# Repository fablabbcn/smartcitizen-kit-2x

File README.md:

# Smart Citizen Kit 2.X

Welcome to the Smart Citizen Kit main repository. Here you will find the hardware design files and the firmware for the SCK 2.1, SCK 2.2 and SCK 2.3 versions. [Click here for version 2.0](https://github.com/fablabbcn/smartcitizen-kit-20)

## Documentation

* If you want to read more about the Smart Citizen Kit or its sensors please check our [documentation](http://docs.smartcitizen.me/)
* If you just want to **upgrade** your Smart Citizen kit **firmware** please refer to the [Upgrading the Smart Citizen Kit Firmware](https://docs.smartcitizen.me/guides/firmware/upgrading-the-firmware/) guide.
* If you want to change something and build the firmware, use the [Building and flashing the Smart Citizen Kit firmware](https://docs.smartcitizen.me/guides/firmware/edit-the-firmware/) guide.
* The SCK provides a comprehensive command shell over USB to manage all the kits functionalities for advanced users: [Using the Smartcitizen Kit shell](https://docs.smartcitizen.me/guides/getting-started/using-the-shell/) guide.
* A compilation of Smartcitizen hardware work in a single **open publication:** [_Hardware X: Special Issue on Open-Hardware for Environmental Sensing and Instruments_](https://doi.org/10.1016/j.ohx.2019.e00070).
* You can also follow the [forum](https://forum.smartcitizen.me/) for updates and ask questions there for support.

## Development

In this repository you can find:

* The Smart Citizen Kit hardware [design files](./hardware).
* The [bootloader](./bootloader) and [main firmware](./sam) (C++) for the SAMD21 microcontroller.
* The [main firmware](./esp) for the ESP8266 microcontroller.
* A [mobile web UI](./mock-api) for setting up the kit.

## Related Smart Citizen repositories

* Platform Core API [github.com/fablabbcn/smartcitizen-api](https://github.com/fablabbcn/smartcitizen-api)
* Platform Web [github.com/fablabbcn/smartcitizen-web](https://github.com/fablabbcn/smartcitizen-web)
* Platform Onboarding [github.com/fablabbcn/smartcitizen-onboarding-app](https://github.com/fablabbcn/smartcitizen-onboarding-app)
* Kit Enclosures [github.com/fablabbcn/smartcitizen-enclosures](https://github.com/fablabbcn/smartcitizen-enclosures)
* Useful software resources for communities [github.com/fablabbcn/smartcitizen-toolkit](https://github.com/fablabbcn/smartcitizen-toolkit)
* Advanced data analysis tools [github.com/fablabbcn/smartcitizen-data](https://github.com/fablabbcn/smartcitizen-data)
* Python API connector [github.com/fablabbcn/smartcitizen-connector](https://github.com/fablabbcn/smartcitizen-connector)
* Analog Sensor Board [github.com/fablabbcn/smartcitizen-analog-sensor-board](https://github.com/fablabbcn/smartcitizen-analog-sensor-board)
* PM Board [github.com/fablabbcn/smartcitizen-kit-pm-board](https://github.com/fablabbcn/smartcitizen-kit-pm-board)

## License

All the software unless stated is released under [GNU GPL v3.0](https://github.com/fablabbcn/smartcitizen-kit-20/blob/master/LICENSE) and the hardware design files under [CERN OHL v1.2](https://github.com/fablabbcn/smartcitizen-kit-20/blob/master/hardware/LICENSE)

## Funding

This work has received funding from the European Union's Horizon 2020 research and innovation program under the grant agreement [No. 689954](https://cordis.europa.eu/project/rcn/202639_en.html)

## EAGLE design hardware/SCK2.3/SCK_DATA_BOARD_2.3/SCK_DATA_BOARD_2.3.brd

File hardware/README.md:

Smart Citizen Kit 2.X Hardware
==============================

This folder contains the Eagle design files for the Smart Citizen Kit 2.X, as well as the silkscreen and manufacturing files:

## SCK 2.1 (discontinued for sensor availability)

- Production files:
    + [SCK 2.1 Data Board production files](SCK2.1/SCK_DATA_BOARD_2.1/SCK_DATA_BOARD_2.1_PRODUCTION.zip)
    + [SCK 2.1 Urban Board production files](SCK2.1/SCK_URBAN_BOARD_2.1/SCK_URBAN_BOARD_2.1_PRODUCTION.zip)
- Design files:
    + [SCK 2.1 Data Board design files](SCK2.1/SCK_DATA_BOARD_2.1)
    + [SCK 2.1 Urban Board design files](SCK2.1/SCK_URBAN_BOARD_2.1)
- [Silkscreen](SCK2.1/SCK_2.1_SILKSCREEN.pdf)
- [Test plan](SCK2.1/test/SCK_2.1_TESTPLAN.pdf), also [at the docs](https://docs.smartcitizen.me/assets/notes/SCK_2.1_TESTPLAN.pdf)
- [Bootloader](SCK2.1/bootloader)

## SCK 2.2 (only for some projects)

- Production files:
    + [SCK 2.2 Data Board production files](SCK2.2/SCK_DATA_BOARD_2.2/SCK_DATA_BOARD_2.2_PRODUCTION.zip)
    + [SCK 2.2 Urban Board production files](SCK2.2/SCK_URBAN_BOARD_2.2/SCK_URBAN_BOARD_2.2_PRODUCTION.zip)
- Design files:
    + [SCK 2.2 Data Board design files](SCK2.2/SCK_DATA_BOARD_2.2)
    + [SCK 2.2 Urban Board design files](SCK2.2/SCK_URBAN_BOARD_2.2)
- [Silkscreen](SCK2.2/SCK2.2_SILKSCREEN.pdf)
- [Test plan](SCK2.2/test/SCK2.2_TESTPLAN.pdf)
- [Bootloader](SCK2.2/bootloader)

## SCK 2.3 (current)

- Production files:
    + [SCK 2.3 Data Board production files](SCK2.3/SCK_DATA_BOARD_2.3/SCK_DATA_BOARD_2.3_PRODUCTION.zip)
    + [SCK 2.3 Urban Board production files](SCK2.3/SCK_URBAN_BOARD_2.3/SCK_URBAN_BOARD_2.3_PRODUCTION.zip)
- Design files:
    + [SCK 2.3 Data Board design files](SCK2.3/SCK_DATA_BOARD_2.3)
    + [SCK 2.3 Urban Board design files](SCK2.3/SCK_URBAN_BOARD_2.3)
- [Test plan](SCK2.3/test/SCK2.3_TESTPLAN.pdf)
- [Bootloader](SCK2.3/bootloader)

Note: for Data Board schematics, see [SCK_DATA_2.1 folder](SCK2.1/SCK_DATA_BOARD_2.1)

## License

All the software is released under [GNU GPL v3.0](../LICENSE) and the hardware design files under [CERN OHL v1.2](LICENSE)

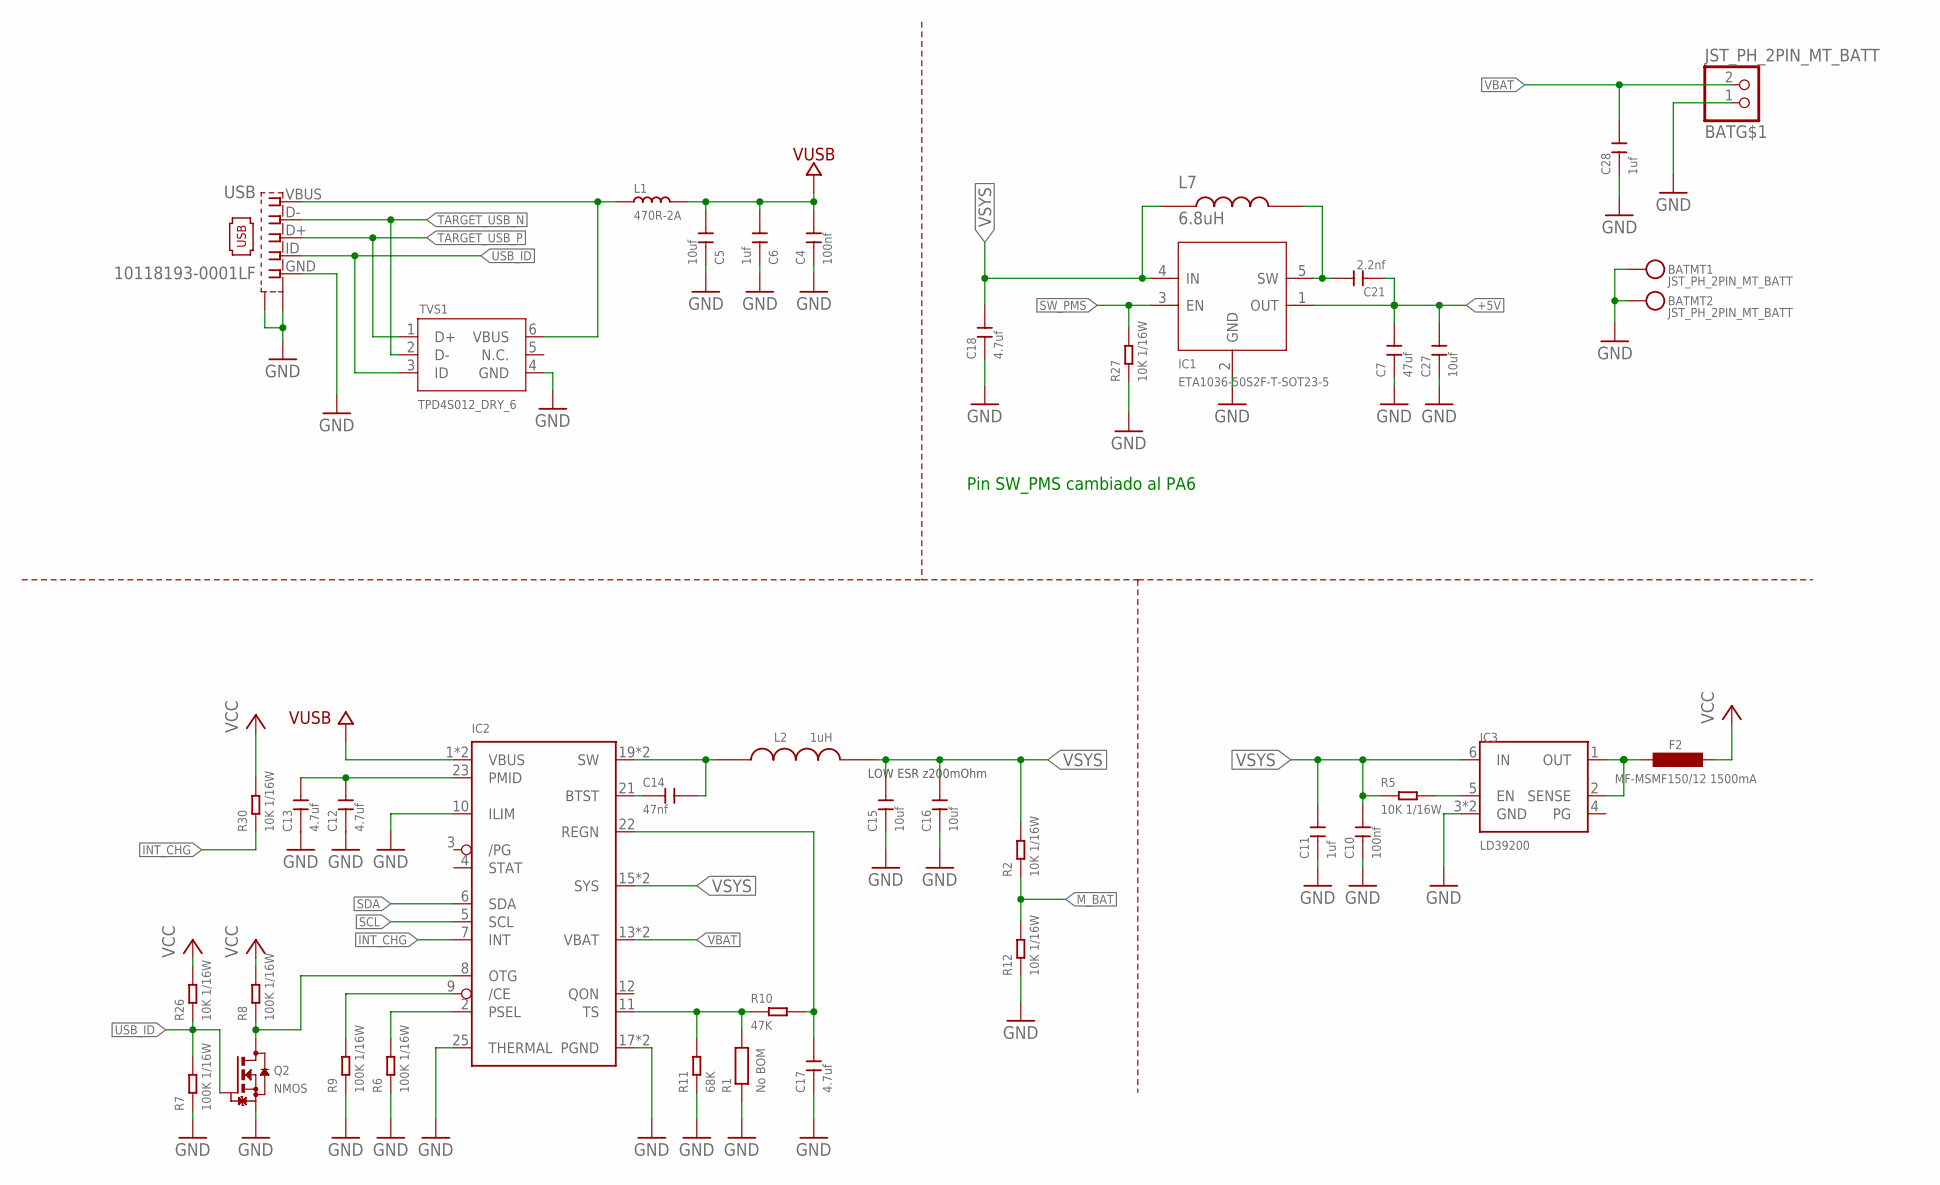
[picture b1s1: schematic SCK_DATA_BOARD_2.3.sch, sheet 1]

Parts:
BAT: JST_PH_2PIN_MT_BATT; JSTPH2_BATT
C4, C10: 100nf; C0402
C5: 10uf; C1206
C6, C11, C28: 1uf; C0805
C7: 47uf; C0805
C12, C13, C17, C18: 4.7uf; C0603
C14: 47nf; C0402
C15, C16, C27: 10uf; C0603
C21: 2.2nf; C0402
F2: MF-MSMF150/12 1500mA; L1812
IC1: ETA1036-50S2F-T-SOT23-5; SOT-23-5
IC2: BQ24259_VQFN(24); 24-PIN_VQFN_THPAD
IC3: LD39200; DFN6_3X3MM
L1: 470R-2A; L0805
L2: 1uH; HANGAR_C1210
L7: 6.8uH; IND_BOURNS_SRN3015TA_3X3_SMD
Q2: NMOS; NMOS_UMT3
R1: No BOM; HANGAR_R0402
R2, R5, R12, R26, R27, R30: 10K 1/16W; R0402
R6, R7, R8, R9: 100K 1/16W; R0402
R10: 47K; R0402
R11: 68K; R0402
TVS1: TPD4S012_DRY_6; DRY6
USB: 10118193-0001LF; CON2_USB_MICRO_B_AT

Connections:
+5V: C7.2, C21.1, C27.2, IC1.1 (OUT); also elsewhere on the board
BTST: C14.1, IC2.21 (BTST)
GND: BAT.1, BAT.NC1, BAT.NC2, C4.1, C5.1, C6.1, C7.1, C10.1, C11.1, C12.1, C13.1, C15.1, C16.1, C17.1, C18.1, C27.1, C28.1, IC1.2 (GND), IC2.10 (ILIM), IC2.17 (PGND), IC2.18 (PGND), IC2.25 (THERMAL), IC3.3 (GND), IC3.7 (GND), Q2.1 (S), R1.1, R6.1, R7.1, R9.1, R11.1, R12.1, R27.1, TVS1.4 (GND), USB.GND (5), USB.P$1 (S1), USB.P$2 (S1), USB.P$3 (S1), USB.P$4 (S1), USB.P$5 (S1), USB.P$6 (S1), USB.P$7 (S1), USB.P$8 (S1), USB.S1 (S2), USB.S2, USB.S3 (S2), USB.S4 (S2), USB.S5 (S2), USB.S6 (S2); also elsewhere on the board
INT_CHG: IC2.7 (INT), R30.1; also elsewhere on the board
M_BAT: R2.1, R12.2; also elsewhere on the board
unnamed: IC3.5 (EN), R5.2
unnamed: L1.1, TVS1.6 (VBUS), USB.VBUS (1)
unnamed: C21.2, IC1.5 (SW), L7.P$2
unnamed: C17.2, IC2.22 (REGN), R10.2
unnamed: C12.2, C13.2, IC2.23 (PMID)
unnamed: IC2.11 (TS), R1.2, R10.1, R11.2
unnamed: IC2.9 (/CE), R9.2
OTG: IC2.8 (OTG), Q2.3 (D), R8.1
PSEL: IC2.2 (PSEL), R6.2
SCL: IC2.5 (SCL); also elsewhere on the board
SDA: IC2.6 (SDA); also elsewhere on the board
SW: C14.2, IC2.19 (SW), IC2.20 (SW), L2.1
SW_PMS: IC1.3 (EN), R27.2; also elsewhere on the board
TARGET_USB_N: TVS1.2 (D-), USB.D- (2); also elsewhere on the board
TARGET_USB_P: TVS1.1 (D+), USB.D+ (3); also elsewhere on the board
USB_ID: Q2.2 (G), R7.2, R26.1, TVS1.3 (ID), USB.ID (4)
VBAT: BAT.2, C28.2, IC2.13 (VBAT), IC2.14 (VBAT)
VCC: F2.1, R8.2, R26.2, R30.2; also elsewhere on the board
VCC_SOURCE: F2.2, IC3.1 (OUT), IC3.2 (SENSE)
VSYS: C10.2, C11.2, C15.2, C16.2, C18.2, IC1.4 (IN), IC2.15 (SYS), IC2.16 (SYS), IC3.6 (IN), L2.2, L7.P$1, R2.2, R5.1
VUSB: C4.2, C5.2, C6.2, IC2.1 (VBUS), IC2.24 (VBUS), L1.2

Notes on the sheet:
LOW ESR z200mOhm
Pin SW_PMS cambiado al PA6

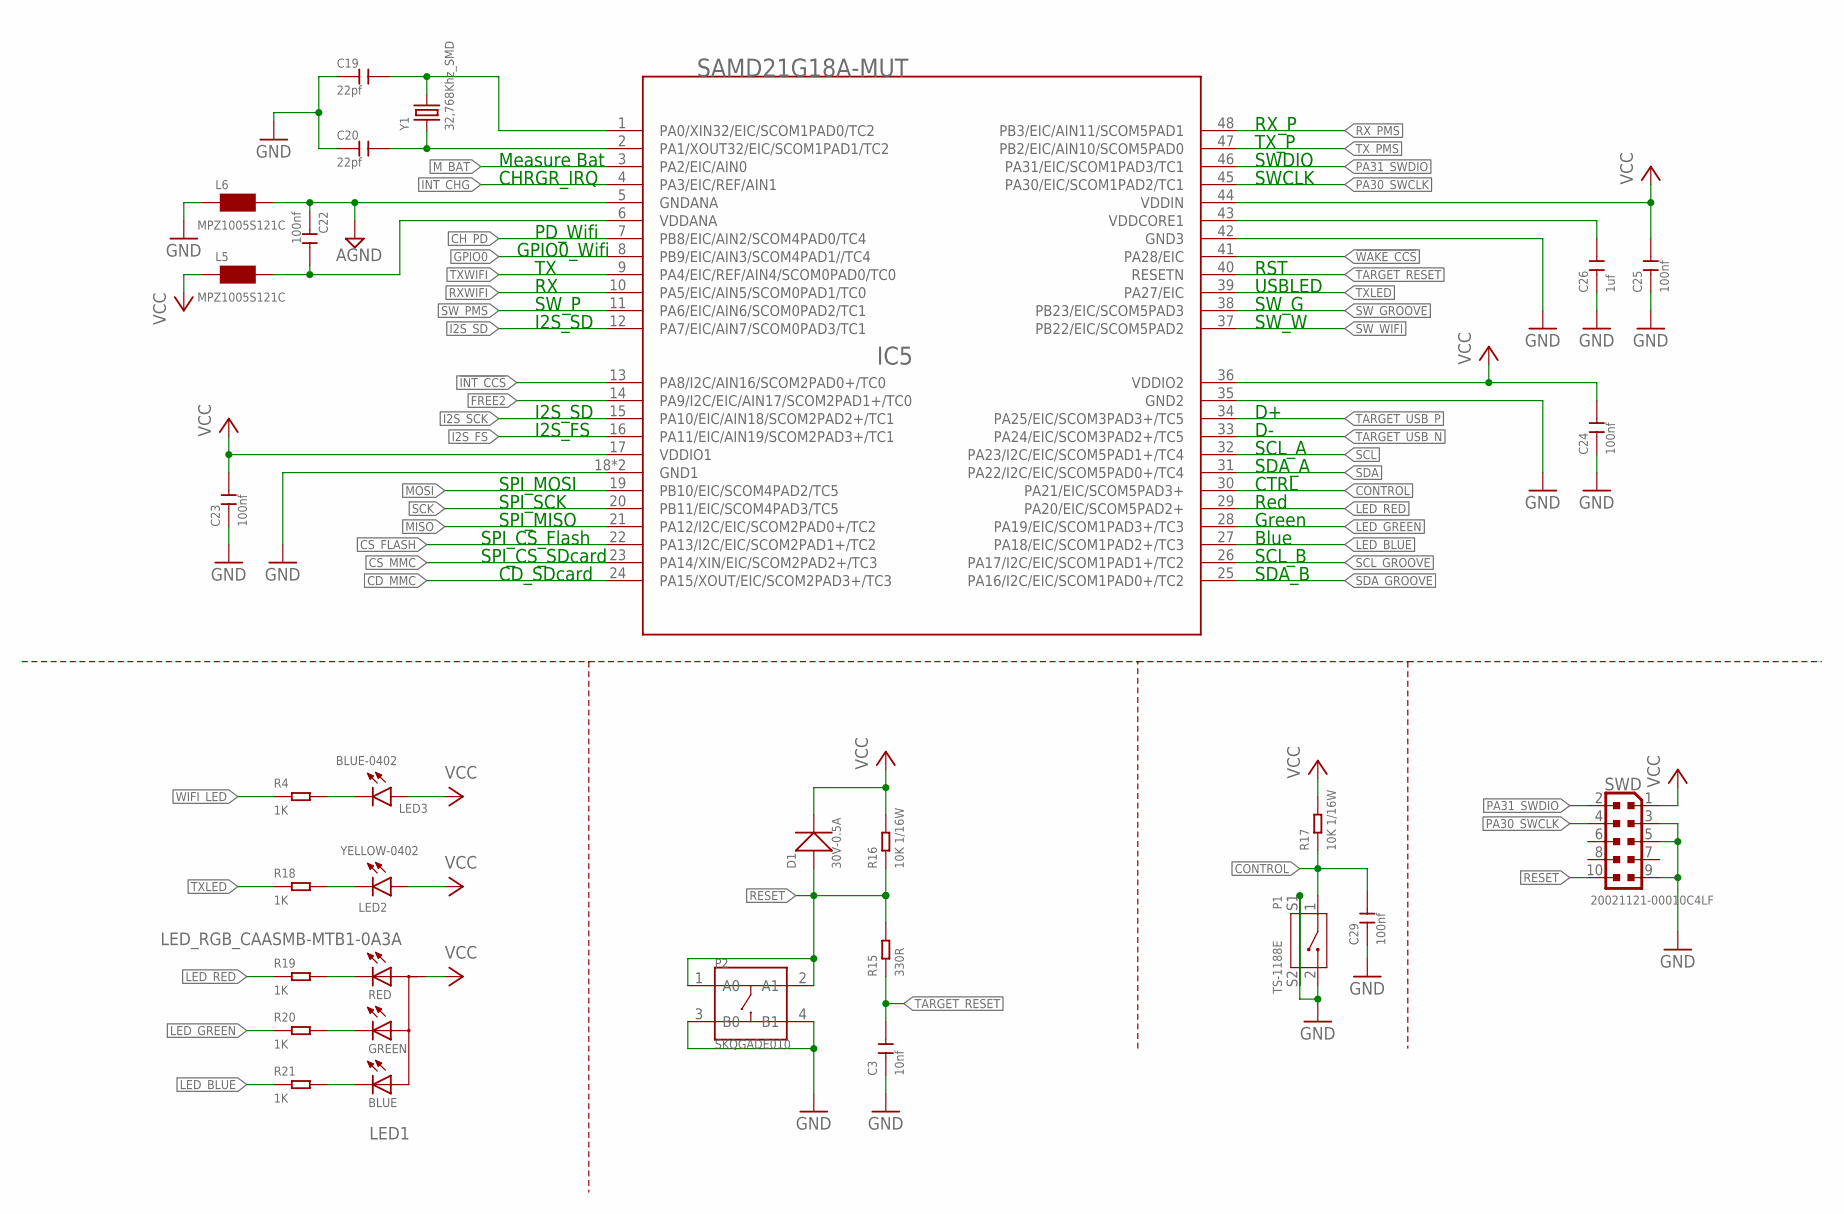
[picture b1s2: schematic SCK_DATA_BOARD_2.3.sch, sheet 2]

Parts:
C3: 10nf; C0402
C19, C20: 22pf; C0402
C22, C23, C24, C25, C29: 100nf; C0402
C26: 1uf; C0805
D1: 30V-0.5A; SOD-323
IC5: SAMD21G18A-MUT; QFN48-7X7
L5, L6: MPZ1005S121C; 0402
LED1: LED_RGB_CAASMB-MTB1-0A3A; HANGAR_P-LCC-4
LED2: YELLOW-0402; CHIPLED_0402_YELLOW
LED3: BLUE-0402; CHIPLED_0402_BLUE
P1: TS-1188E; SW4-SMD-7.0X3.5X3.5MM-90D
P2: SKQGADE010; SW4-SMD-5.2X5.2X1.5MM
R4, R18, R19, R20, R21: 1K; R0402
R15: 330R; R0402
R16, R17: 10K 1/16W; R0402
SWD: 20021121-00010C4LF; 2X05_SMD_1.27MM
Y1: 32,768Khz_SMD; CRISTALLI_RESONATOR_EPSON_FC_145

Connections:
!INT_CCS: IC5.13 (PA8/I2C/AIN16/SCOM2PAD0+/TC0); also elsewhere on the board
!WAKE_CCS: IC5.41 (PA28/EIC); also elsewhere on the board
AGND: C22.1, IC5.5 (GNDANA), L6.2
AVCC: C22.2, IC5.6 (VDDANA), L5.2
CD_MMC: IC5.24 (PA15/XOUT/EIC/SCOM2PAD3+/TC3); also elsewhere on the board
CH_PD: IC5.7 (PB8/EIC/AIN2/SCOM4PAD0/TC4); also elsewhere on the board
CONTROL: C29.2, IC5.30 (PA21/EIC/SCOM5PAD3+), P1.1, R17.1
CS_FLASH: IC5.22 (PA13/I2C/EIC/SCOM2PAD1+/TC2); also elsewhere on the board
CS_MMC: IC5.23 (PA14/XIN/EIC/SCOM2PAD2+/TC3); also elsewhere on the board
FREE2: IC5.14 (PA9/I2C/EIC/AIN17/SCOM2PAD1+/TC0); also elsewhere on the board
GND: C3.1, C19.1, C20.1, C23.1, C24.1, C25.1, C26.1, C29.1, IC5.18 (GND1), IC5.35 (GND2), IC5.42 (GND3), IC5.TP (GND1), L6.1, P1.2, P1.S1, P1.S2, P2.3 (B0), P2.4 (B1), SWD.3, SWD.5, SWD.9; also elsewhere on the board
GPIO0: IC5.8 (PB9/EIC/AIN3/SCOM4PAD1//TC4); also elsewhere on the board
I2S_FS: IC5.16 (PA11/EIC/AIN19/SCOM2PAD3+/TC1); also elsewhere on the board
I2S_SCK: IC5.15 (PA10/EIC/AIN18/SCOM2PAD2+/TC1); also elsewhere on the board
I2S_SD: IC5.12 (PA7/EIC/AIN7/SCOM0PAD3/TC1); also elsewhere on the board
INT_CHG: IC5.4 (PA3/EIC/REF/AIN1); also elsewhere on the board
LED_BLUE: IC5.27 (PA18/EIC/SCOM1PAD2+/TC3), R21.1
LED_GREEN: IC5.28 (PA19/EIC/SCOM1PAD3+/TC3), R20.1
LED_RED: IC5.29 (PA20/EIC/SCOM5PAD2+), R19.1
MISO: IC5.21 (PA12/I2C/EIC/SCOM2PAD0+/TC2); also elsewhere on the board
MOSI: IC5.19 (PB10/EIC/SCOM4PAD2/TC5); also elsewhere on the board
M_BAT: IC5.3 (PA2/EIC/AIN0); also elsewhere on the board
unnamed: LED2.K (C), R18.2
unnamed: LED1.2 (GREEN), R20.2
unnamed: LED3.K (C), R4.2
unnamed: LED1.1 (RED), R19.2
unnamed: LED1.3 (BLUE), R21.2
PA00_XIN32: C19.2, IC5.1 (PA0/XIN32/EIC/SCOM1PAD0/TC2), Y1.P$2 (2)
PA01_XOUT32: C20.2, IC5.2 (PA1/XOUT32/EIC/SCOM1PAD1/TC2), Y1.P$1 (1)
PA30_SWCLK: IC5.45 (PA30/EIC/SCOM1PAD2/TC1), SWD.4
PA31_SWDIO: IC5.46 (PA31/EIC/SCOM1PAD3/TC1), SWD.2
RESET: D1.+, P2.1 (A0), P2.2 (A1), R15.2, R16.1, SWD.10; also elsewhere on the board
RXWIFI: IC5.10 (PA5/EIC/AIN5/SCOM0PAD1/TC0); also elsewhere on the board
RX_PMS: IC5.48 (PB3/EIC/AIN11/SCOM5PAD1); also elsewhere on the board
SCK: IC5.20 (PB11/EIC/SCOM4PAD3/TC5); also elsewhere on the board
SCL: IC5.32 (PA23/I2C/EIC/SCOM5PAD1+/TC4); also elsewhere on the board
SCL_GROOVE: IC5.26 (PA17/I2C/EIC/SCOM1PAD1+/TC2); also elsewhere on the board
SDA: IC5.31 (PA22/I2C/EIC/SCOM5PAD0+/TC4); also elsewhere on the board
SDA_GROOVE: IC5.25 (PA16/I2C/EIC/SCOM1PAD0+/TC2); also elsewhere on the board
SW_GROOVE: IC5.38 (PB23/EIC/SCOM5PAD3); also elsewhere on the board
SW_PMS: IC5.11 (PA6/EIC/AIN6/SCOM0PAD2/TC1); also elsewhere on the board
SW_WIFI: IC5.37 (PB22/EIC/SCOM5PAD2); also elsewhere on the board
TARGET_RESET: C3.2, IC5.40 (RESETN), R15.1
TARGET_USB_N: IC5.33 (PA24/EIC/SCOM3PAD2+/TC5); also elsewhere on the board
TARGET_USB_P: IC5.34 (PA25/EIC/SCOM3PAD3+/TC5); also elsewhere on the board
TXLED: IC5.39 (PA27/EIC), R18.1
TXWIFI: IC5.9 (PA4/EIC/REF/AIN4/SCOM0PAD0/TC0); also elsewhere on the board
TX_PMS: IC5.47 (PB2/EIC/AIN10/SCOM5PAD0); also elsewhere on the board
VCC: C23.2, C24.2, C25.2, D1.-, IC5.17 (VDDIO1), IC5.36 (VDDIO2), IC5.44 (VDDIN), L5.1, LED1.4 (A), LED2.A, LED3.A, R16.2, R17.2, SWD.1; also elsewhere on the board
VDDCORE: C26.2, IC5.43 (VDDCORE1)
WIFI_LED: R4.1; also elsewhere on the board

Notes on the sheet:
Blue
Green
SCL_B
SDA_B
Red
CTRL
SW_G
SW_W
SDA_A
SCL_A
USBLED
RST
SWDIO
SWCLK
PD_Wifi
GPIO0_Wifi
I2S_SD
Measure Bat
CHRGR_IRQ
I2S_FS
SPI_MOSI
SPI_SCK
SPI_MISO
SPI_CS_Flash
SPI_CS_SDcard
CD_SDcard
SW_P
RX_P
TX_P

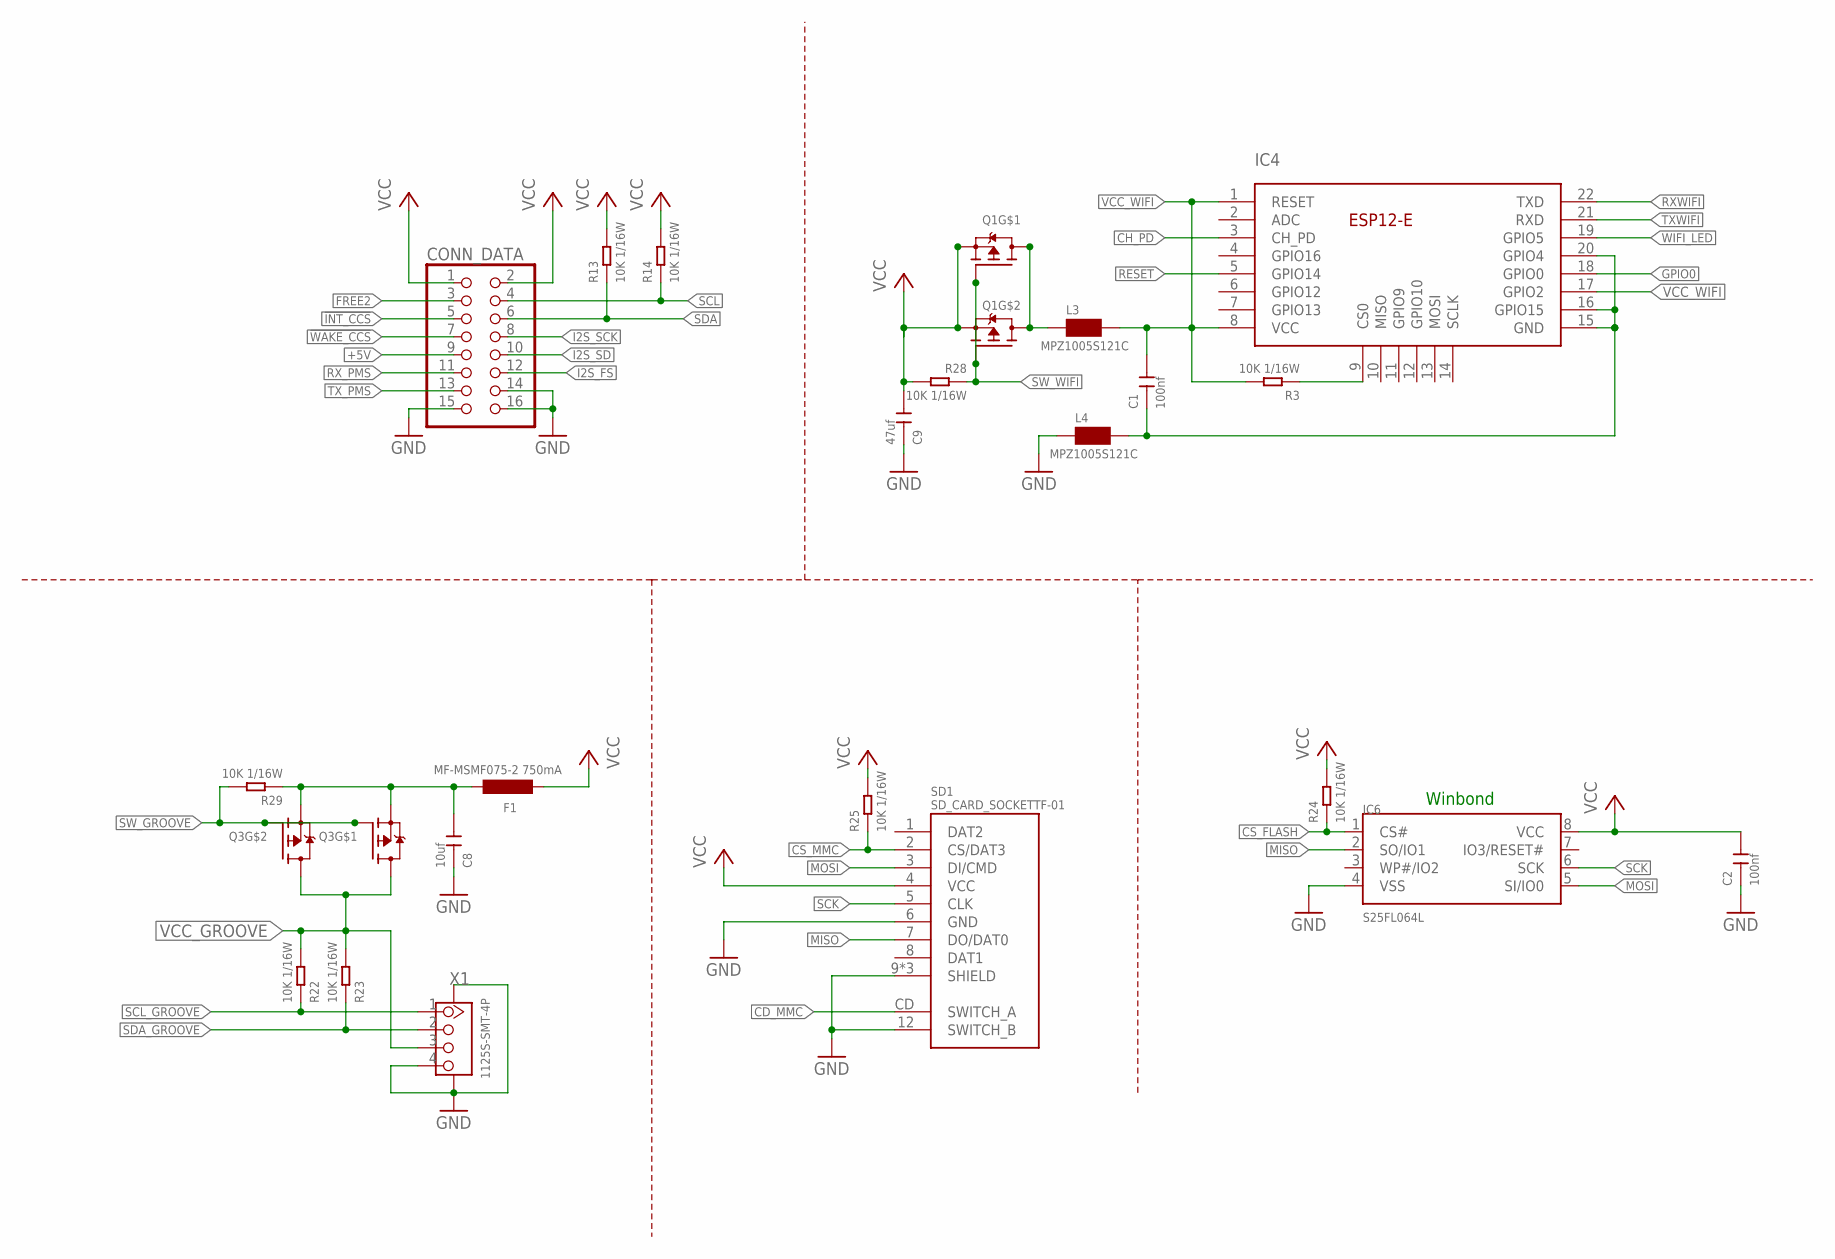
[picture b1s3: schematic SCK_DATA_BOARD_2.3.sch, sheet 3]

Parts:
C1, C2: 100nf; C0402
C8: 10uf; C1206
C9: 47uf; C1210
CONN_DATA: PINHD_2X8FEM_SMD; PINHD_2X8_SMD_FEMALE_UNHOLED
F1: MF-MSMF075-2 750mA; L1812
IC4: HANGAR_ESP-12-E; HANGAR_ESP12-E
IC6: S25FL064L; SOIC_8-208MILS
L3, L4: MPZ1005S121C; 0402
Q1: PMOS; POWERPAK-SC70-6L; MPN SIA923AEDJ-T1-GE3
Q3: PMOS; POWERPAK-SC70-6L
R3, R13, R14, R22, R23, R24, R25, R28, R29: 10K 1/16W; R0402
SD1: SD_CARD_SOCKETTF-01; TF-01; MPN 320090008
X1: 1125S-SMT-4P; CONNECTOR-NEW_HW4-SMD-2.0; MPN 320110030

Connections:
!INT_CCS: CONN_DATA.5; also elsewhere on the board
!WAKE_CCS: CONN_DATA.7; also elsewhere on the board
+5V: CONN_DATA.9; also elsewhere on the board
CD_MMC: SD1.CD (SWITCH_A); also elsewhere on the board
CH_PD: IC4.3 (CH_PD); also elsewhere on the board
CS_FLASH: IC6.1 (CS#), R24.1; also elsewhere on the board
CS_MMC: R25.1, SD1.2 (CS/DAT3); also elsewhere on the board
FREE2: CONN_DATA.3; also elsewhere on the board
GND: C2.1, C8.1, C9.1, CONN_DATA.14, CONN_DATA.15, CONN_DATA.16, IC6.4 (VSS), L4.2, SD1.6 (GND), SD1.9 (SHIELD), SD1.10 (SHIELD), SD1.11 (SHIELD), SD1.12 (SWITCH_B), X1.4, X1.SS1, X1.SS2; also elsewhere on the board
GND_WIFI: C1.1, IC4.15 (GND), IC4.16 (GPIO15), IC4.20 (GPIO4), L4.1
GPIO0: IC4.18 (GPIO0); also elsewhere on the board
I2S_FS: CONN_DATA.12; also elsewhere on the board
I2S_SCK: CONN_DATA.8; also elsewhere on the board
I2S_SD: CONN_DATA.10; also elsewhere on the board
MISO: IC6.2 (SO/IO1), SD1.7 (DO/DAT0); also elsewhere on the board
MOSI: IC6.5 (SI/IO0), SD1.3 (DI/CMD); also elsewhere on the board
unnamed: L3.2, Q1.3 (D), Q1.6 (D), Q1.TP1 (D), Q1.TP2 (D)
unnamed: IC4.9 (CS0), R3.1
RESET: IC4.5 (GPIO14); also elsewhere on the board
RXWIFI: IC4.22 (TXD); also elsewhere on the board
RX_PMS: CONN_DATA.11; also elsewhere on the board
SCK: IC6.6 (SCK), SD1.5 (CLK); also elsewhere on the board
SCL: CONN_DATA.4, R14.1; also elsewhere on the board
SCL_GROOVE: R22.1, X1.1; also elsewhere on the board
SDA: CONN_DATA.6, R13.1; also elsewhere on the board
SDA_GROOVE: R23.1, X1.2; also elsewhere on the board
SW_GROOVE: Q3.2 (G), Q3.5 (G), R29.2; also elsewhere on the board
SW_WIFI: Q1.2 (G), Q1.5 (G), R28.1; also elsewhere on the board
TXWIFI: IC4.21 (RXD); also elsewhere on the board
TX_PMS: CONN_DATA.13; also elsewhere on the board
VCC: C2.2, C9.2, CONN_DATA.1, CONN_DATA.2, F1.2, IC6.8 (VCC), Q1.1 (S), Q1.4 (S), R13.2, R14.2, R24.2, R25.2, R28.2, SD1.4 (VCC); also elsewhere on the board
VCC_GROOVE: Q3.3 (D), Q3.6 (D), Q3.TP1 (D), Q3.TP2 (D), R22.2, R23.2, X1.3
VCC_GROOVE_0: C8.2, F1.1, Q3.1 (S), Q3.4 (S), R29.1
VCC_WIFI: C1.2, IC4.1 (RESET), IC4.8 (VCC), IC4.17 (GPIO2), L3.1, R3.2
WIFI_LED: IC4.19 (GPIO5); also elsewhere on the board

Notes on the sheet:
Winbond

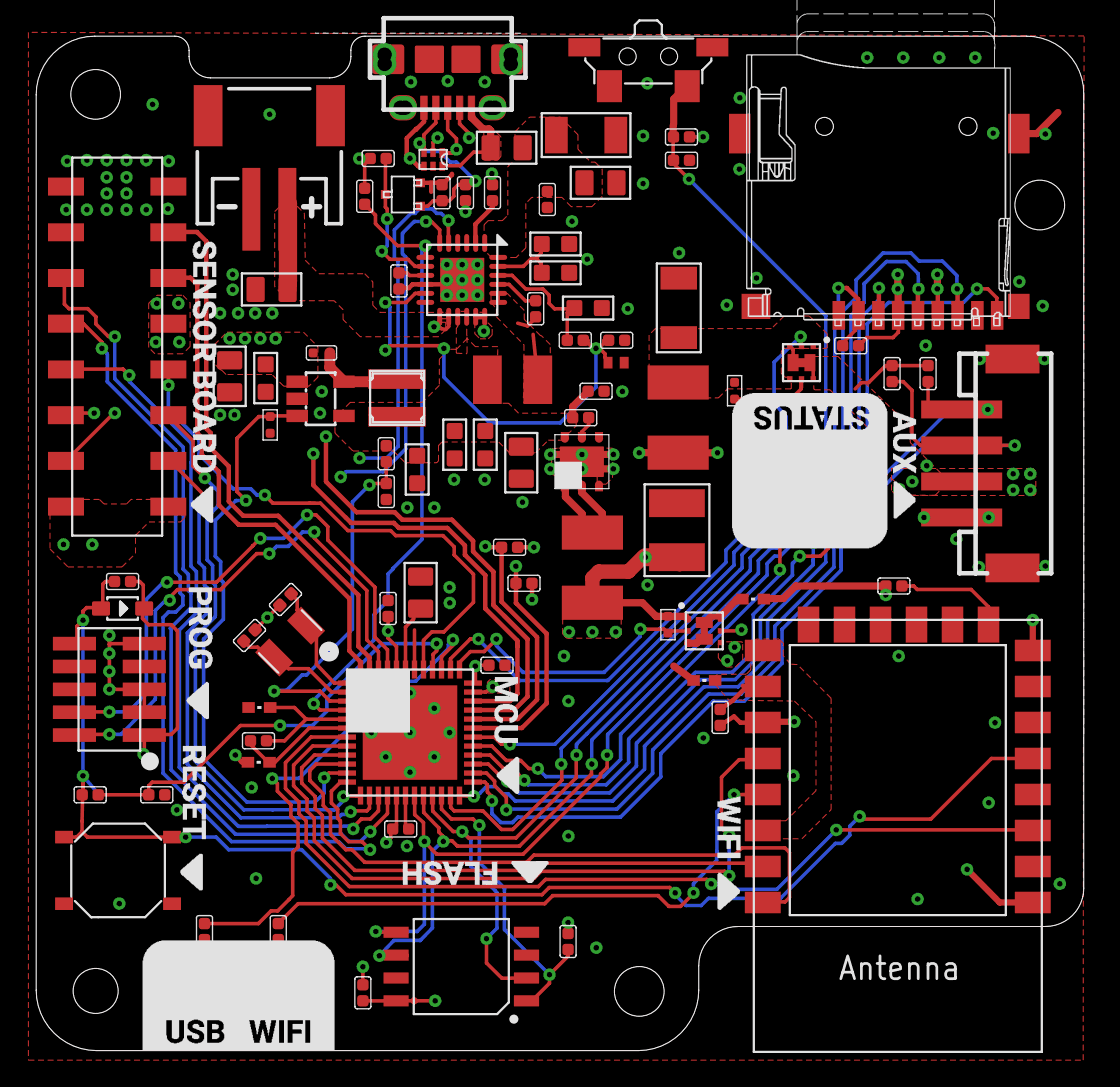
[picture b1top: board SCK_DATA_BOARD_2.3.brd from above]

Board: 4 copper layers, 58.2 x 56.4 mm, 91 parts (0 on the bottom side), 74 nets.

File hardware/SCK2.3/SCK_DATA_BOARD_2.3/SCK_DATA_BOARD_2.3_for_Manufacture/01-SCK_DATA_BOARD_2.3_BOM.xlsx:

Quantity | Designator | Value/Tolerance | Footprint | Manufacturer | Manufacturer Part Number | Description | Seeed OPL
17 | R2, R3, R5, R12, R13, R14, R16, R17, R22, R23, R24, R25, R26, R27, R28, R29, R30 | 10K 1/16W | R0402 | Yageo | RC0402FR-0710KL | SMD-RES-10K-1%-1/16W(0402) | 301010047
5 | R4, R18, R19, R20, R21 | 1K | R0402 | Yageo | RC0402JR-071KL | SMD-RES-1K-5%-1/16W(0402) | 301010006
4 | R6, R7, R8, R9 | 100K 1/16W | R0402 | Yageo | RC0402JR-07100KL | SMD-RES-100K-5%-1/16W(0402) | 301010033
1 | R10 | 47K | R0402 | Yageo | RC0402JR-0747KL | SMD-RES-47K-5%-1/16W(0402) | 301010005
1 | R11 | 68K | R0402 | Yageo | RC0402JR-0768KL | SMD-RES-68K-50V-5%(0402) | 301010496
1 | R15 | 330R | R0402 | Yageo | RC0402FR-07330RL | SMD-RES-330R-1%-1/16W(0402) | 301010466
9 | C1, C2, C4, C10, C22, C23, C24, C25, C29 | 100nf | C0402 | Yageo | CC0402KRX7R8BB104 | CERAMIC-100NF-25V-10%-X7R(0402) | 302010024
1 | C3 | 10nf | C0402 | Yageo | CC0402KRX7R9BB103 | CERAMIC-10NF-50V-10%-X7R(0402) | 302010006
2 | C5, C8 | 10uf | C1206 | Yageo | CC1206KKX5R8BB106 | CERAMIC-10UF-25V-10%-X5R(1206) | 302010181
1 | C7 | 47uf | C0805 | Yageo | CC0805MKX5R5BB476 | CERAMIC-47UF-6.3V-20%-X5R(0805) | 302010166
1 | C9 | 47uf | C1210 | Murata Electronics North America | GRM32ER71A476ME15L | CERAMIC-47UF-10V-20%-X7R(1210) | 302010252
4 | C6, C11, C26, C28 | 1uf | C0805 | Yageo | CC0805KKX7R8BB105 | CERAMIC-1UF-25V-10%-X7R(0805) | 302010179
4 | C12, C13, C17, C18 | 4.7uf | C0603 | Yageo | CC0603KRX5R6BB475 | CERAMIC-4.7UF-10V-10%-X5R(0603) | 302010111
1 | C14 | 47nf | C0402 | Yageo | CC0402KRX7R8BB473 | CERAMIC-47NF-25V-10%-X7R(0402) | 302010002
3 | C15, C16, C27 | 10uf | C0603 | Yageo | CC0603KRX5R6BB106 | CERAMIC-10UF-10V-10%-X5R(0603) | 302010103
2 | C19, C20 | 22pf | C0402 | Yageo | CC0402JRNPO9BN220 | CERAMIC-22PF-50V-5%-NPO(0402) | 302010018
1 | C21 | 2.2nf | C0402 | Yageo | CC0402KRX7R9BB222 | CERAMIC-2.2NF-50V-10%-X7R(0402) | 302010022
1 | L1 | SMD Ferrite Bead 470R-2A | L0805 | WELL | WLB2012-471T20 | SMD Ferrite Bead 470R-2A | 303030008
4 | L3, L4, L5, L6 | MPZ1005S121C | L0402 | TDK Corporation | MPZ1005S121CT000 | FERRITE BEAD 120 OHM 0402 1LN
1 | L2 | 1uH 2.5A | L1210 | Murata Electronics North America | LQH32PN1R0NNCL | FIXED IND 1UH 2.5A 43.2 MOHM SMD
1 | L7 | 6.8uH 1A | L1212 | Bourns Inc. | SRN3015TA-6R8M | FIXED IND 6.8UH 1A 160 MOHM SMD
1 | D1 | 30V-0.5A | SOD-323-2 | Leshan Radio | LRB551V-30T1G | SMD-DIODE-SCHOTTKY-30V-0.5A(SOD-323) | 304020004
1 | Y1 | Crystal 32,768Khz | FC_135 | Abracon LLC | ABS07-32.768KHZ-T | CRYSTAL 32.7680KHZ 12.5PF SMD | 306010055
1 | IC1 | PMIC | SOT-23-5 | ETA Solutions | ETA1036-50S2F-T | PMIC-ETA1036-50S2F-T(SOT23-5) | 310030153
1 | IC2 | IC CHARGER | 24-PIN_VQFN_THPAD | Texas Instruments | BQ24259RGER | IC CHARGER NVDC-1 USB I2C 24VQFN
1 | IC3 | IC REG 3.3V 2A | DFN6_3X3MM | STMicroelectronics | LD39200PU33R | IC REG LINEAR 3.3V 2A 6DFN
1 | IC4 | WIFI MODULE | ESP-12F |  | ESP-12F | ESP8266 WiFi/802.11 Module
1 | IC5 | IC MCU | QFN48-7X7 | Microchip Technology | ATSAMD21G18A-MUT | IC MCU 32BIT 256KB FLASH 48QFN | 310010095
1 | IC6 | IC FLASH | SOIC8 | Cypress Semiconductor Corp | S25FL064LABMFI010 | IC FLASH 64M SPI 108MHZ 8SOIC
1 | LED1 | RGB LED PLCC4 | PLCC-4 | Broadcom Limited | ASMB-MTB1-0B3A2 | Standard LEDs - SMD PLCC4,T/Mt,BS/WF Silicone RGB
1 | LED2 | LED YELLOW 0402 SMD | DIODE_0402_R | Vishay Semiconductor Opto Division | VLMY1500-GS08 | LED YELLOW 0402 SMD | 304090016
1 | LED3 | LED BLUE 0402 SMD | DIODE_0402_R | Vishay Semiconductor Opto Division | VLMB1500-GS08 | LED BLUE 0402 SMD | 304090075
1 | F1 | PTC RESET FUSE 13.2V 750MA 1812 | L1812 | Bourns Inc. | MF-MSMF075-2 | PTC RESET FUSE 13.2V 750MA 1812
1 | F2 | PTC RESET FUSE 12V 1.5A 1812 | L1812 | Bourns Inc. | MF-MSMF150/12-2 | PTC RESET FUSE 12V 1.5A 1812
2 | Q1, Q3 | MOSFET 2P-CH 20V 4.5A SC70-6L | SC70-6L | Vishay Siliconix | SIA923AEDJ-T1-GE3 | MOSFET 2P-CH 20V 4.5A SC70-6L
1 | Q2 | MOSFET Nch 30V Vdss SOT-323 SC-70; 300mA Id | SOT323-3 | ROHM Semiconductor | RJU003N03FRAT106 | MOSFET Nch 30V Vdss SOT-323 SC-70; 300mA Id
1 | P1 | SMD Button Side Plast;SPST;180gf | TS-1188E | ShenZhen Best Electronics | TS-1188E | SMD Button Side Plast;SPST;180gf | 311020023
1 | P2 | Tactile Switches 5.2x5.2x1.5mm 260gf | SW4-SMD-5.2X5.2X1.5MM | ALPS | SKQGADE010 | Tactile Switches 5.2x5.2x1.5mm 260gf | 311020017
1 | SD1 | SD_CARD_SOCKETTF-01 | TF-01 | ShenZhen Best Electronics | TF-01 | SD_CARD_SOCKETTF-01 | 320090008
1 | TVS1 | SMD Diode TVS;4-Ch USB ESD Solution with-SON-6（1.45x1） | DRY6 | Texas Instruments | TPD4S012DRYR | SMD Diode TVS;4-Ch USB ESD Solution with-SON-6（1.45x1） | 304050020
1 | BAT | CONN HEADER SMD R/A 2POS 2MM | S2B-PH | JST | S2B-PH-SM4-TB(LF)(SN) | CONN HEADER SMD R/A 2POS 2MM | 320110026
1 | CONN_DATA | CONN HDR 16POS 0.1 TIN SMD | PINHD_2X8_SMD_FEMALE_UNHOLED | Sullins Connector Solutions | NPTC082KFMS-RC | CONN HDR 16POS 0.1 TIN SMD
1 | USB | CONN RCPT USB2.0 MICRO B SMD R/A | USB_MICRO_B_AT | Amphenol ICC (FCI) | 10118193-0001LF | CONN RCPT USB2.0 MICRO B SMD R/A | 320010005
1 | X1 | SMD Grove Female Header-Beige;4P-2.0 | HW4-SMD-2.0 | TAIFENG | 1125S-SMT-4P | SMD Grove Female Header-Beige;4P-2.0 | 320110030
1 | SWD | CONN HEADER SMD 10POS 1.27MM | 2X05_SMD_1.27MM | Amphenol ICC (FCI) | 20021121-00010C4LF | CONN HEADER SMD 10POS 1.27MM | 320020119

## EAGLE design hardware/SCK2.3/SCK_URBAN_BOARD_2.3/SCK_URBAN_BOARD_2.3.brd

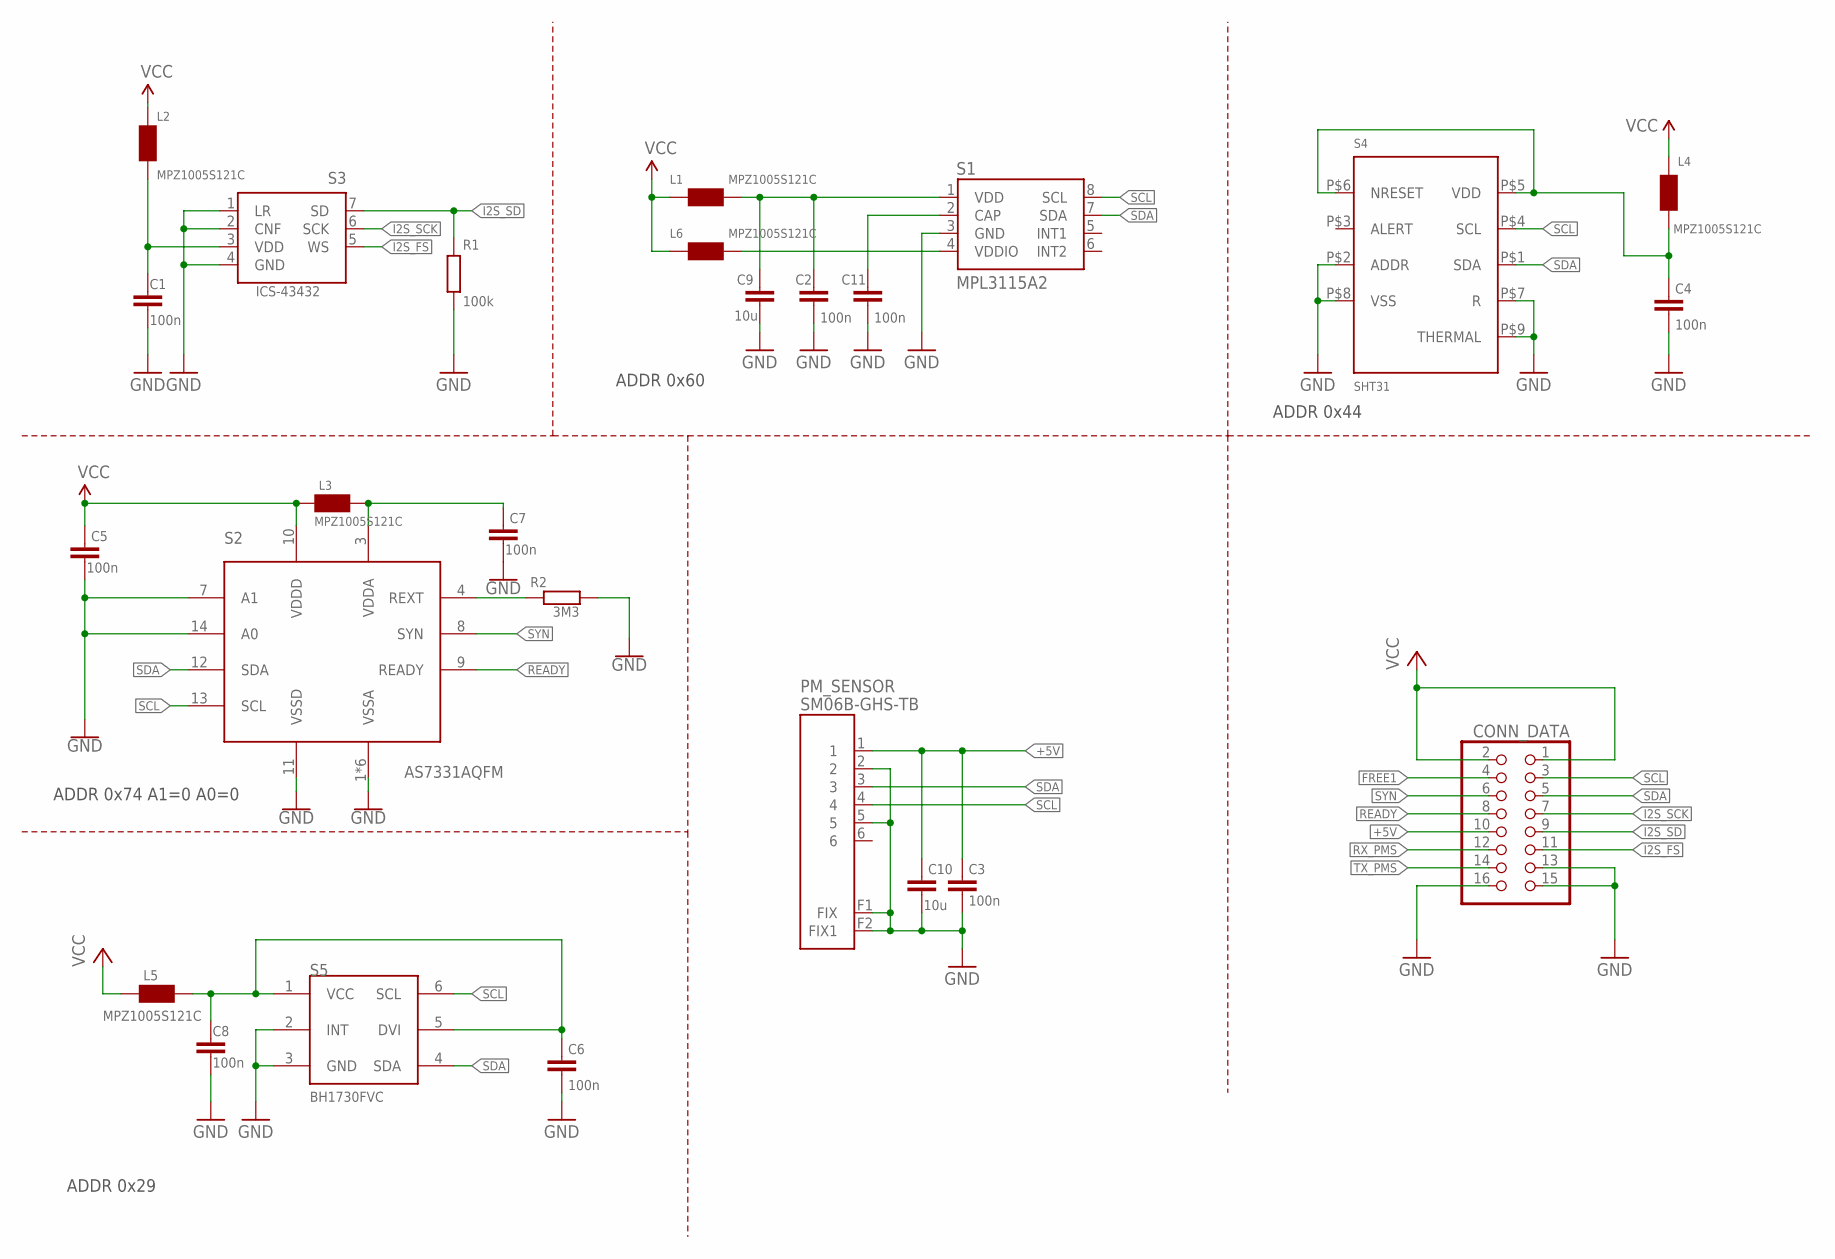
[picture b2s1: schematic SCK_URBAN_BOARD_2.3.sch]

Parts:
C1, C2, C3, C4, C5, C6, C7, C8, C11: 100n; C0402
C9, C10: 10u; C0603
CONN_DATA: PINHD_2X8MAL_SMD; PINHD_2X8_SMD_MALE_UNHOLED
L1, L2, L3, L4, L5, L6: MPZ1005S121C; L0402
PM_SENSOR: SM06B-GHS-TB
R1: 100k; R0402
R2: 3M3; R0402
S1: MPL3115A2
S2: AS7331AQFM; OLGA16
S3: ICS-43432
S4: SHT31; DFN8_STH3X-DIS
S5: BH1730FVC; WSOF6

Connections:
+5V: C3.2, C10.2, CONN_DATA.10, PM_SENSOR.1
FREE1: CONN_DATA.4
GND: C1.1, C2.1, C3.1, C4.1, C5.1, C6.1, C7.1, C8.1, C9.1, C10.1, C11.1, CONN_DATA.13, CONN_DATA.15, CONN_DATA.16, PM_SENSOR.2, PM_SENSOR.5, PM_SENSOR.F1 (FIX), PM_SENSOR.F2 (FIX1), R1.1, R2.2, S1.3 (GND), S2.1 (VSSA), S2.2 (VSSA), S2.5 (VSSA), S2.6 (VSSA), S2.7 (A1), S2.11 (VSSD), S2.14 (A0), S2.15 (VSSA), S2.16 (VSSA), S3.1 (LR), S3.2 (CNF), S3.4 (GND), S4.P$2 (ADDR), S4.P$7 (R), S4.P$8 (VSS), S4.P$9 (THERMAL), S5.2 (INT), S5.3 (GND)
I2S_FS: CONN_DATA.11, S3.5 (WS)
I2S_SCK: CONN_DATA.7, S3.6 (SCK)
I2S_SD: CONN_DATA.9, R1.2, S3.7 (SD)
unnamed: C7.2, L3.1, S2.3 (VDDA)
unnamed: R2.1, S2.4 (REXT)
unnamed: C6.2, C8.2, L5.2, S5.1 (VCC), S5.5 (DVI)
unnamed: C11.2, S1.2 (CAP)
unnamed: C4.2, L4.2, S4.P$5 (VDD), S4.P$6 (NRESET)
unnamed: L6.2, S1.4 (VDDIO)
unnamed: C2.2, C9.2, L1.2, S1.1 (VDD)
unnamed: C1.2, L2.2, S3.3 (VDD)
READY: CONN_DATA.8, S2.9 (READY)
RX_PMS: CONN_DATA.12
SCL: CONN_DATA.3, PM_SENSOR.4, S1.8 (SCL), S2.13 (SCL), S4.P$4 (SCL), S5.6 (SCL)
SDA: CONN_DATA.5, PM_SENSOR.3, S1.7 (SDA), S2.12 (SDA), S4.P$1 (SDA), S5.4 (SDA)
SYN: CONN_DATA.6, S2.8 (SYN)
TX_PMS: CONN_DATA.14
VCC: C5.2, CONN_DATA.1, CONN_DATA.2, L1.1, L2.1, L3.2, L4.1, L5.1, L6.1, S2.10 (VDDD)

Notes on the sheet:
ADDR 0x44
ADDR 0x29
ADDR 0x74 A1=0 A0=0
ADDR 0x60

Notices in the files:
parts and their libraries:
SparkFun-PowerSymbols: Licensing: Creative Commons ShareAlike 4.0 International - https://creativecommons.org/licenses/by-sa/4.0
